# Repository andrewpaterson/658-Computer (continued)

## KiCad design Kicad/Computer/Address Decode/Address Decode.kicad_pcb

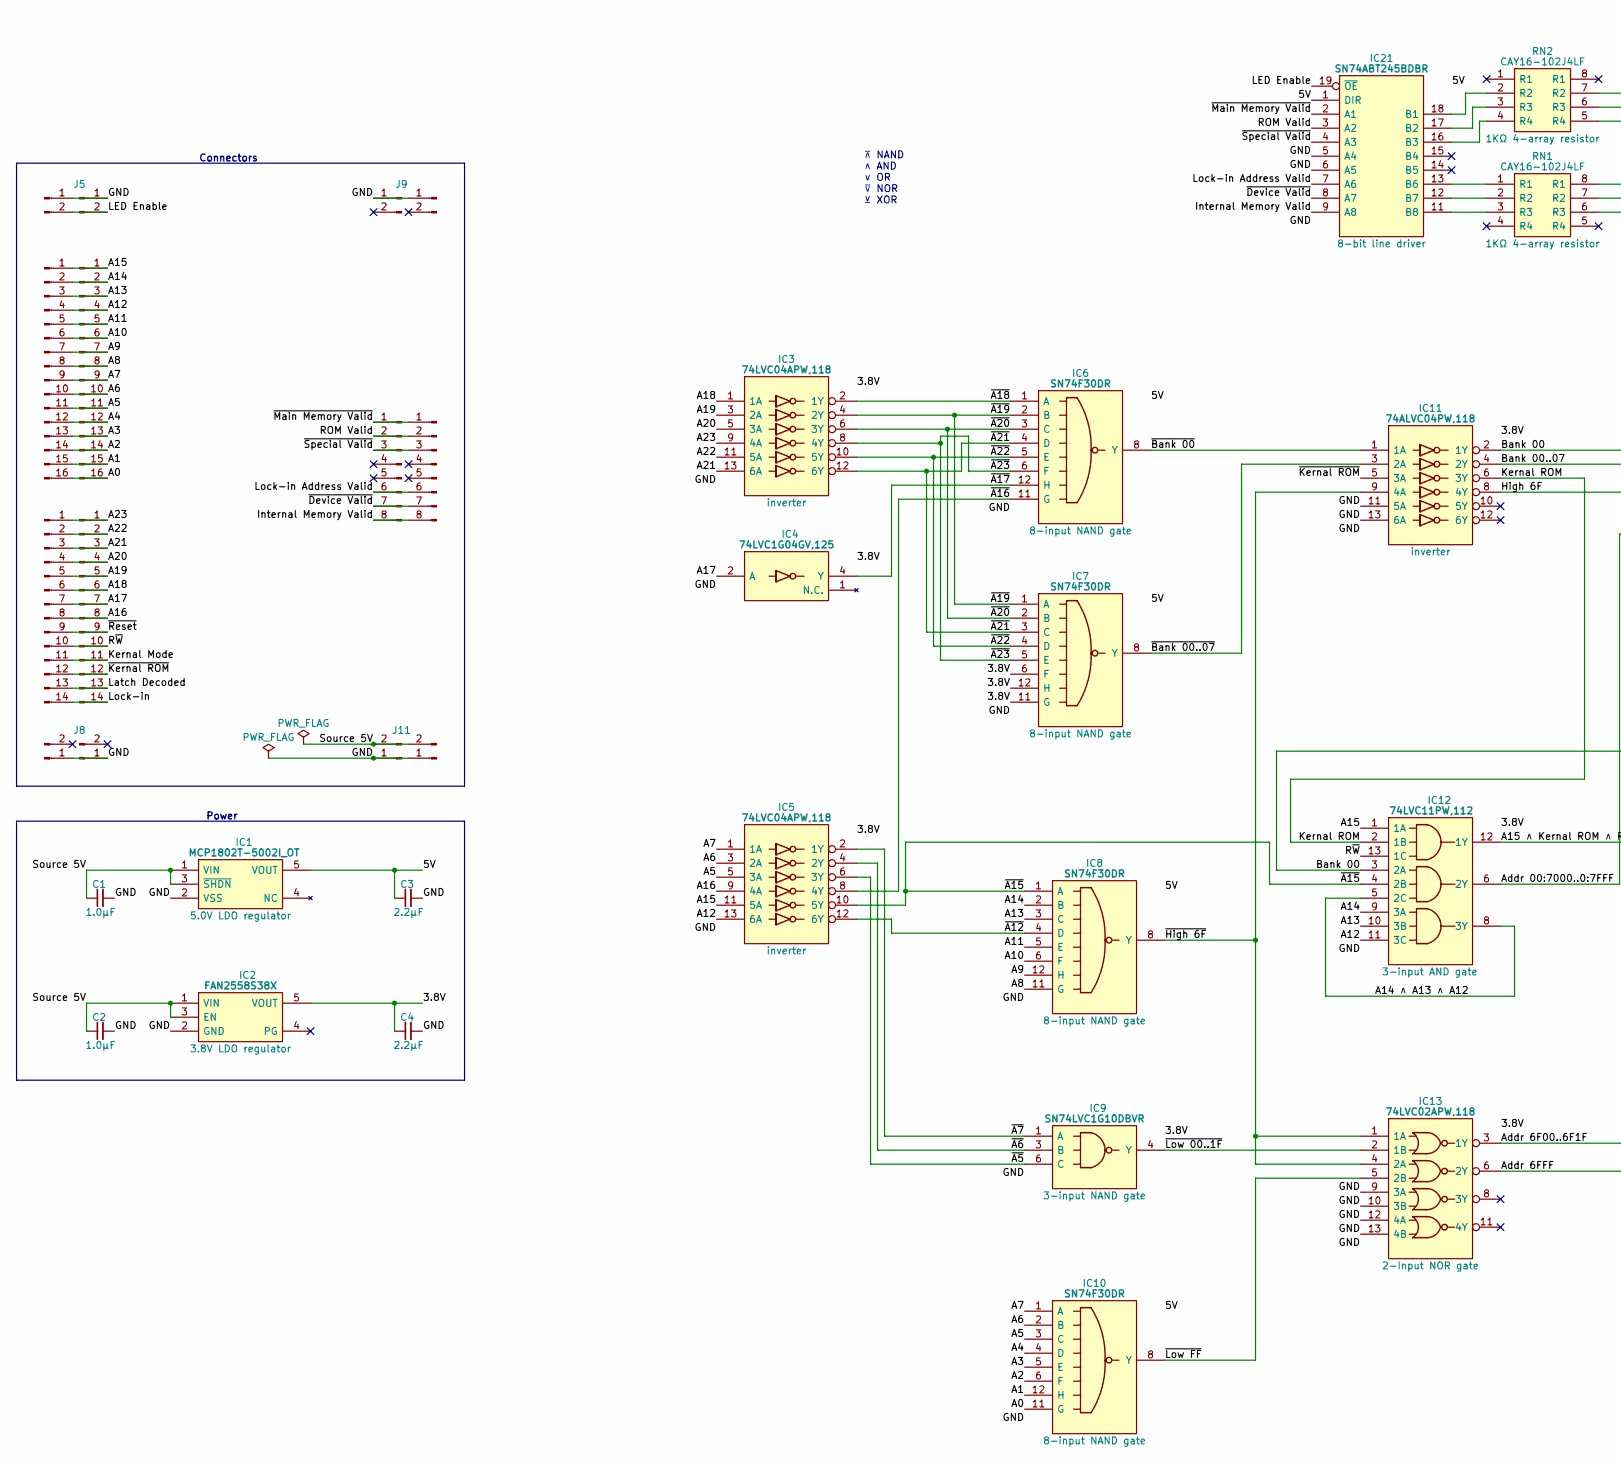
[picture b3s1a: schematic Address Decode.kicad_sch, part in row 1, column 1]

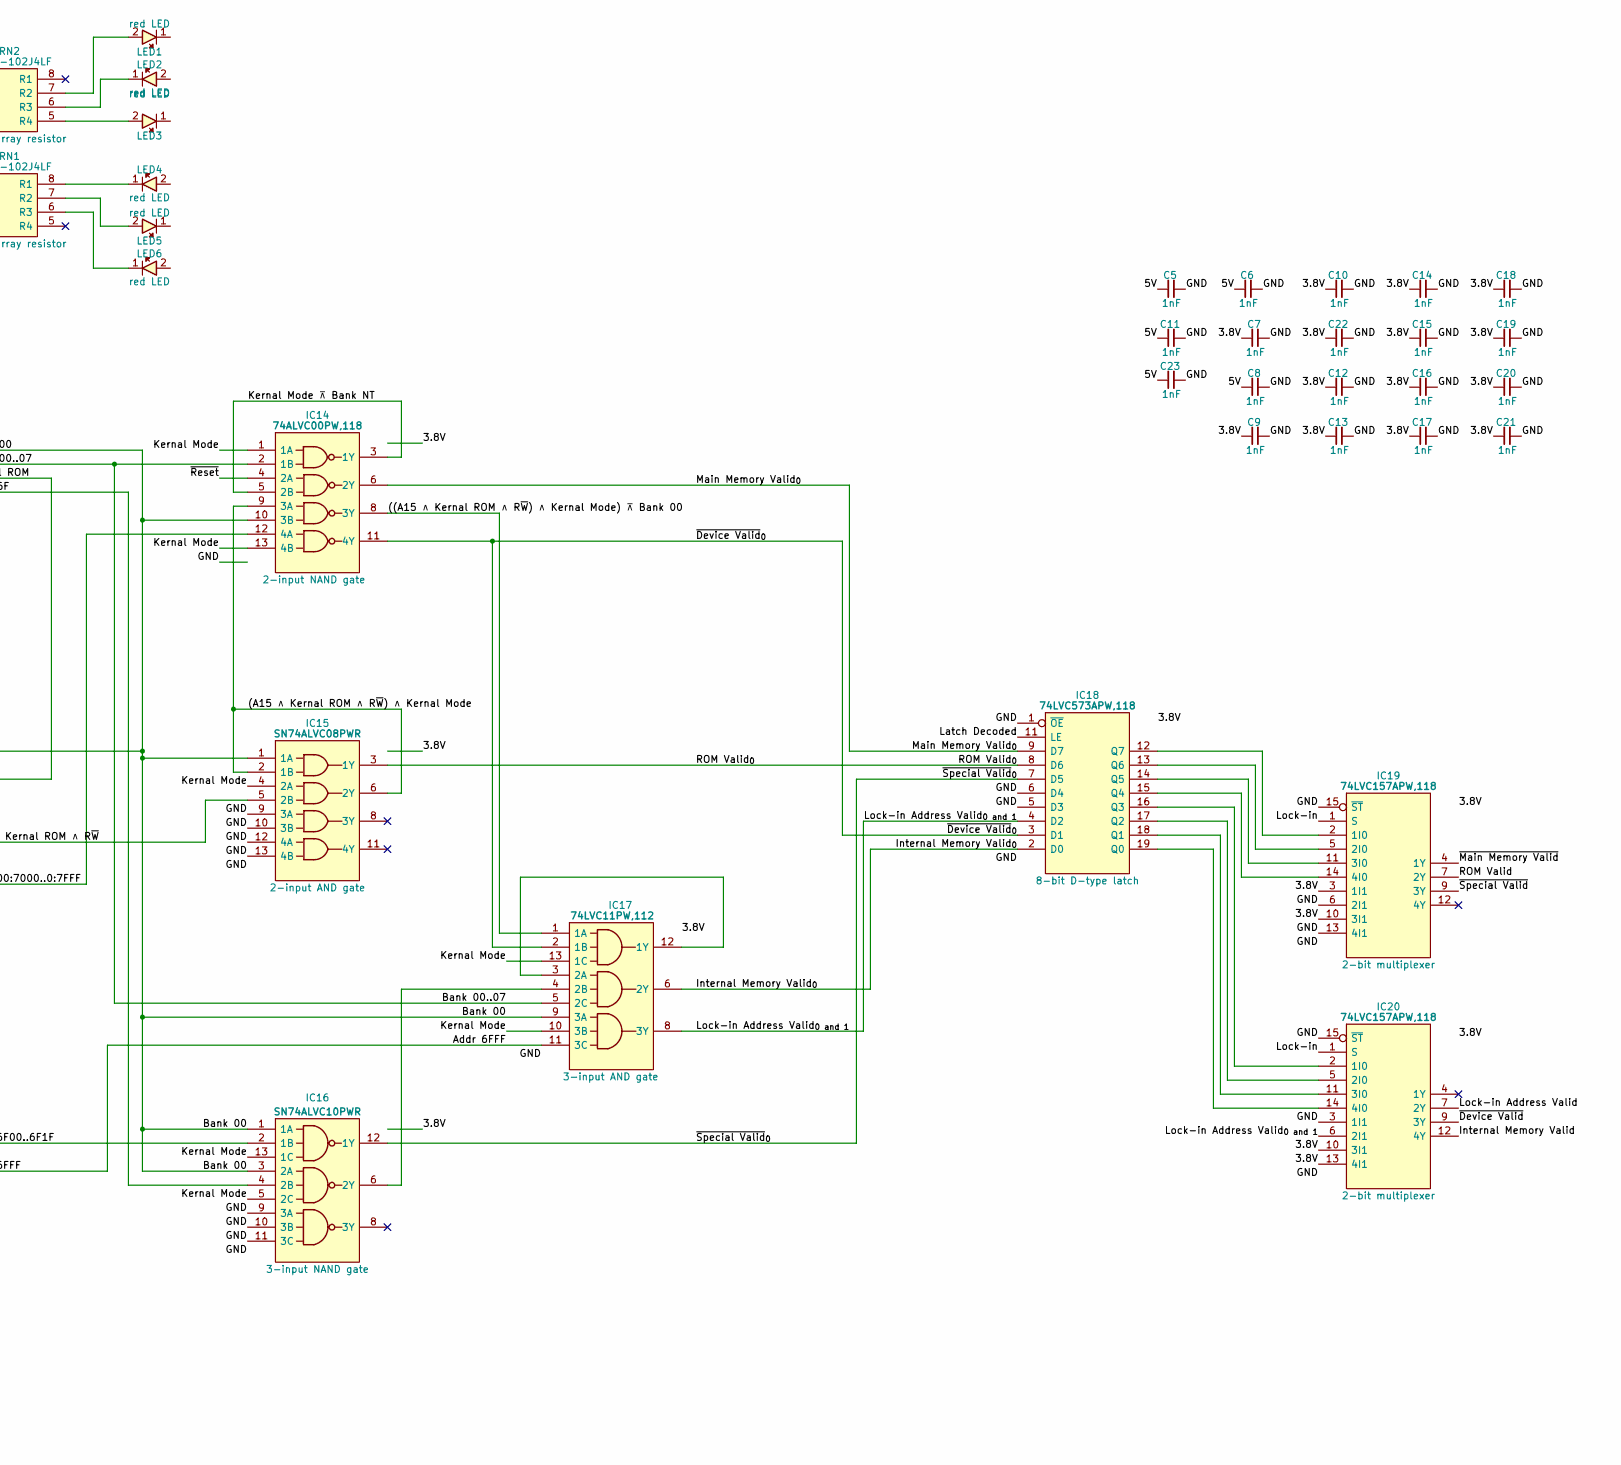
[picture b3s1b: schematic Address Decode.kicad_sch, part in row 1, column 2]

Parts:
C1, C2, C3, C4, C5, C6, C7, C8, C9, C10, C11, C12, C13, C14, C15, C16, C17, C18, C19, C20, C21, C22, C23: C_0805
IC1: MCP1802T-5002I_OT; SOT95P270X145-5N; Manufacturer_Part_Number MCP1802T-5002I/OT; Mouser Part Number 579-MCP1802T-5002IOT
IC2: FAN2558S38X; SOT95P270X145-5N; Manufacturer_Part_Number FAN2558S38X; Mouser Part Number 512-FAN2558S38X
IC3, IC5: 74LVC04APW,118; SOP65P640X110-14N; Manufacturer_Part_Number 74LVC04APW,118; Mouser Part Number 771-74LVC04APW-T
IC4: 74LVC1G04GV,125; SOT95P275X110-5N; Manufacturer_Part_Number 74LVC1G04GV,125; Mouser Part Number 771-74LVC1G04GV
IC6, IC7, IC8, IC10: SN74F30DR; SOIC127P600X175-14N; Manufacturer_Part_Number SN74F30DR; Mouser Part Number 595-SN74F30DR
IC9: SN74LVC1G10DBVR; SOT95P280X145-6N; Manufacturer_Part_Number SN74LVC1G10DBVR; Mouser Part Number 595-SN74LVC1G10DBVR
IC11: 74ALVC04PW,118; SOP65P640X110-14N; Manufacturer_Part_Number 74ALVC04PW,118; Mouser Part Number 771-ALVC04PW118
IC12, IC17: 74LVC11PW,112; SOP65P640X110-14N; Mouser Part Number 771-LVC11PW112
IC13: 74LVC02APW,118; SOP65P640X110-14N; Mouser Part Number 771-74LVC02APW-T
IC14: 74ALVC00PW,118; SOP65P640X110-14N; Mouser Part Number 771-ALVC00PW118
IC15: SN74ALVC08PWR; SOP65P640X120-14N; Manufacturer_Part_Number SN74ALVC08PWR; Mouser Part Number 595-SN74ALVC08PWR
IC16: SN74ALVC10PWR; SOP65P640X120-14N; Manufacturer_Part_Number SN74ALVC10PWR
IC18: 74LVC573APW,118; SOP65P640X110-20N; Mouser Part Number 771-74LVC573APW-T
IC19, IC20: 74LVC157APW,118; SOP65P640X110-16N; Mouser Part Number 771-74LVC157APW-T
IC21: SN74ABT245BDBR; SOP65P780X200-20N; Manufacturer_Part_Number SN74ABT245BDBR; Mouser Part Number 595-SN74ABT245BDBR
J1, J4, J5, J8, J9, J11, J12, J14: Conn_01x02_Male; PinHeader_1x02_P2.54mm_Vertical
J2, J6: Conn_01x16_Male; PinHeader_1x16_P2.54mm_Vertical
J3, J7: Conn_01x14_Male; PinHeader_1x14_P2.54mm_Vertical
J10, J13: Conn_01x08_Male; PinHeader_1x08_P2.54mm_Vertical
LED1, LED2, LED3, LED4, LED5, LED6: 150224SS73100; 150224SS73100A; Manufacturer_Part_Number 150224SS73100; Mouser Part Number 710-150224SS73100
RN1, RN2: CAY16-102J4LF; CAY16-J4; Manufacturer_Part_Number CAY16-102J4LF; Mouser Part Number 652-CAY16-102J4LF

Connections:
/3.8V: C4.1, C7.1, C9.1, C10.1, C12.1, C13.1, C14.1, C15.1, C16.1, C17.1, C18.1, C19.1, C20.1, C21.1, C22.1, IC2.5 (VOUT), IC3.14 (3V), IC4.5 (3V), IC5.14 (3V), IC7.6 (F), IC7.11 (G), IC7.12 (H), IC9.5 (3V), IC11.14 (3V), IC12.14 (3V), IC13.14 (3V), IC14.14 (3V), IC15.14 (3V), IC16.14 (3V), IC17.14 (3V), IC18.20 (3V), IC19.3 (1I1), IC19.10 (3I1), IC19.16 (3V), IC20.10 (3I1), IC20.13 (4I1), IC20.16 (3V)
/5V: C3.1, C5.1, C6.1, C8.1, C11.1, C23.1, IC1.5 (VOUT), IC6.14 (5V), IC7.14 (5V), IC8.14 (5V), IC10.14 (5V), IC21.1 (DIR), IC21.20 (5V)
/((A15 ∧ Kernal ROM ∧ R~W) ∧ Kernal Mode) ⊼ Bank 00: IC14.8 (3Y), IC17.1 (1A)
/(A15 ∧ Kernal ROM ∧ R~W) ∧ Kernal Mode: IC14.9 (3A), IC15.2 (1B), IC15.6 (2Y)
/A0: IC10.11 (G), J2.16, J6.16
/A1: IC10.12 (H), J2.15, J6.15
/A2: IC10.6 (F), J2.14, J6.14
/A3: IC10.5 (E), J2.13, J6.13
/A4: IC10.4 (D), J2.12, J6.12
/A5: IC5.5 (3A), IC10.3 (C), J2.11, J6.11
/A6: IC5.3 (2A), IC10.2 (B), J2.10, J6.10
/A7: IC5.1 (1A), IC10.1 (A), J2.9, J6.9
/A8: IC8.11 (G), J2.8, J6.8
/A9: IC8.12 (H), J2.7, J6.7
/A10: IC8.6 (F), J2.6, J6.6
/A11: IC8.5 (E), J2.5, J6.5
/A12: IC5.13 (6A), IC12.11 (3C), J2.4, J6.4
/A13: IC8.3 (C), IC12.10 (3B), J2.3, J6.3
/A14: IC8.2 (B), IC12.9 (3A), J2.2, J6.2
/A14 ∧ A13 ∧ A12: IC12.5 (2C), IC12.8 (3Y)
/A15: IC5.11 (5A), IC12.1 (1A), J2.1, J6.1
/A15 ∧ Kernal ROM ∧ R~W: IC12.12 (1Y), IC15.5 (2B)
/A16: IC5.9 (4A), J3.8, J7.8
/A17: IC4.2 (A), J3.7, J7.7
/A18: IC3.1 (1A), J3.6, J7.6
/A19: IC3.3 (2A), J3.5, J7.5
/A20: IC3.5 (3A), J3.4, J7.4
/A21: IC3.13 (6A), J3.3, J7.3
/A22: IC3.11 (5A), J3.2, J7.2
/A23: IC3.9 (4A), J3.1, J7.1
/Addr 00:7000..0:7FFF: IC12.6 (2Y), IC14.12 (4A)
/Addr 6F00..6F1F: IC13.3 (1Y), IC16.2 (1B)
/Addr 6FFF: IC13.6 (2Y), IC17.11 (3C)
/Bank 00: IC11.2 (1Y), IC12.3 (2A), IC14.10 (3B), IC15.1 (1A), IC16.1 (1A), IC16.3 (2A), IC17.9 (3A)
/Bank 00..07: IC11.4 (2Y), IC14.2 (1B), IC17.5 (2C)
/GND: C1.2, C2.2, C3.2, C4.2, C5.2, C6.2, C7.2, C8.2, C9.2, C10.2, C11.2, C12.2, C13.2, C14.2, C15.2, C16.2, C17.2, C18.2, C19.2, C20.2, C21.2, C22.2, C23.2, IC1.2 (VSS), IC2.2 (GND), IC3.7 (GND), IC4.3 (GND), IC5.7 (GND), IC6.7 (GND), IC7.7 (GND), IC8.7 (GND), IC9.2 (GND), IC10.7 (GND), IC11.7 (GND), IC11.11 (5A), IC11.13 (6A), IC12.7 (GND), IC13.7 (GND), IC13.9 (3A), IC13.10 (3B), IC13.12 (4A), IC13.13 (4B), IC14.7 (GND), IC15.7 (GND), IC15.9 (3A), IC15.10 (3B), IC15.12 (4A), IC15.13 (4B), IC16.7 (GND), IC16.9 (3A), IC16.10 (3B), IC16.11 (3C), IC17.7 (GND), IC18.1 (~OE), IC18.5 (D3), IC18.6 (D4), IC18.10 (GND), IC19.6 (2I1), IC19.8 (GND), IC19.13 (4I1), IC19.15 (~ST), IC20.3 (1I1), IC20.8 (GND), IC20.15 (~ST), IC21.5 (A4), IC21.6 (A5), IC21.10 (GND), J1.1, J4.1, J5.1, J8.1, J9.1, J11.1, J12.1, J14.1
/High 6F: IC11.8 (4Y), IC16.4 (2B)
/Internal Memory Valid: IC20.12 (4Y), IC21.9 (A8), J10.8, J13.8
/Internal Memory Valid_{0}: IC17.6 (2Y), IC18.2 (D0)
/Kernal Mode: IC14.1 (1A), IC14.13 (4B), IC15.4 (2A), IC16.5 (2C), IC16.13 (1C), IC17.10 (3B), IC17.13 (1C), J3.11, J7.11
/Kernal Mode ⊼ Bank NT: IC14.3 (1Y), IC14.5 (2B)
/Kernal ROM: IC11.6 (3Y), IC12.2 (1B)
/LED Enable: IC21.19 (~OE), J1.2, J5.2
/Latch Decoded: IC18.11 (LE), J3.13, J7.13
/Lock-in: IC19.1 (S), IC20.1 (S), J3.14, J7.14
/Lock-in Address Valid: IC20.7 (2Y), IC21.7 (A6), J10.6, J13.6
/Lock-in Address Valid_{0 and 1}: IC17.8 (3Y), IC18.4 (D2), IC20.6 (2I1)
/Main Memory Valid_{0}: IC14.6 (2Y), IC18.9 (D7)
/ROM Valid: IC19.7 (2Y), IC21.3 (A2), J10.2, J13.2
/ROM Valid_{0}: IC15.3 (1Y), IC18.8 (D6)
/R~W: IC12.13 (1C), J3.10, J7.10
/Source 5V: C1.1, C2.1, IC1.1 (VIN), IC1.3 (~SHDN), IC2.1 (VIN), IC2.3 (EN), J11.2, J14.2
/~A5: IC5.6 (3Y), IC9.6 (C)
/~A6: IC5.4 (2Y), IC9.3 (B)
/~A7: IC5.2 (1Y), IC9.1 (A)
/~A12: IC5.12 (6Y), IC8.4 (D)
/~A15: IC5.10 (5Y), IC8.1 (A), IC12.4 (2B)
/~A16: IC5.8 (4Y), IC6.11 (G)
/~A17: IC4.4 (Y), IC6.12 (H)
/~A18: IC3.2 (1Y), IC6.1 (A)
/~A19: IC3.4 (2Y), IC6.2 (B), IC7.1 (A)
/~A20: IC3.6 (3Y), IC6.3 (C), IC7.2 (B)
/~A21: IC3.12 (6Y), IC6.4 (D), IC7.3 (C)
/~A22: IC3.10 (5Y), IC6.5 (E), IC7.4 (D)
/~A23: IC3.8 (4Y), IC6.6 (F), IC7.5 (E)
/~Bank 00..07: IC7.8 (Y), IC11.3 (2A)
/~Bank 00: IC6.8 (Y), IC11.1 (1A)
/~Device Valid: IC20.9 (3Y), IC21.8 (A7), J10.7, J13.7
/~Device Valid_{0}: IC14.11 (4Y), IC17.2 (1B), IC18.3 (D1)
/~High 6F: IC8.8 (Y), IC11.9 (4A), IC13.1 (1A), IC13.4 (2A)
/~Kernal ROM: IC11.5 (3A), J3.12, J7.12
/~Low 00..1F: IC9.4 (Y), IC13.2 (1B)
/~Low FF: IC10.8 (Y), IC13.5 (2B)
/~Main Memory Valid: IC19.4 (1Y), IC21.2 (A1), J10.1, J13.1
/~Reset: IC14.4 (2A), J3.9, J7.9
/~Special Valid: IC19.9 (3Y), IC21.4 (A3), J10.3, J13.3
/~Special Valid_{0}: IC16.12 (1Y), IC18.7 (D5)
unnamed: IC16.6 (2Y), IC17.4 (2B)
unnamed: IC17.3 (2A), IC17.12 (1Y)
unnamed: IC18.12 (Q7), IC19.2 (1I0)
unnamed: IC18.13 (Q6), IC19.5 (2I0)
unnamed: IC18.14 (Q5), IC19.11 (3I0)
unnamed: IC18.15 (Q4), IC19.14 (4I0)
unnamed: IC18.16 (Q3), IC20.2 (1I0)
unnamed: IC18.17 (Q2), IC20.5 (2I0)
unnamed: IC18.18 (Q1), IC20.11 (3I0)
unnamed: IC18.19 (Q0), IC20.14 (4I0)
unnamed: IC21.11 (B8), RN1.3 (R3)
unnamed: IC21.12 (B7), RN1.2 (R2)
unnamed: IC21.13 (B6), RN1.1 (R1)
unnamed: IC21.16 (B3), RN2.4 (R4)
unnamed: IC21.17 (B2), RN2.3 (R3)
unnamed: IC21.18 (B1), RN2.2 (R2)
unnamed: LED2.1, RN2.6 (R3)
unnamed: LED4.1, RN1.8 (R1)
unnamed: LED6.1, RN1.6 (R3)
unnamed: LED5.2, RN1.7 (R2)
unnamed: LED3.2, RN2.5 (R4)
unnamed: LED1.2, RN2.7 (R2)

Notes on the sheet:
⊼ NAND ∧ AND ∨ OR ⊽ NOR ⊻ XOR
Connectors
Power

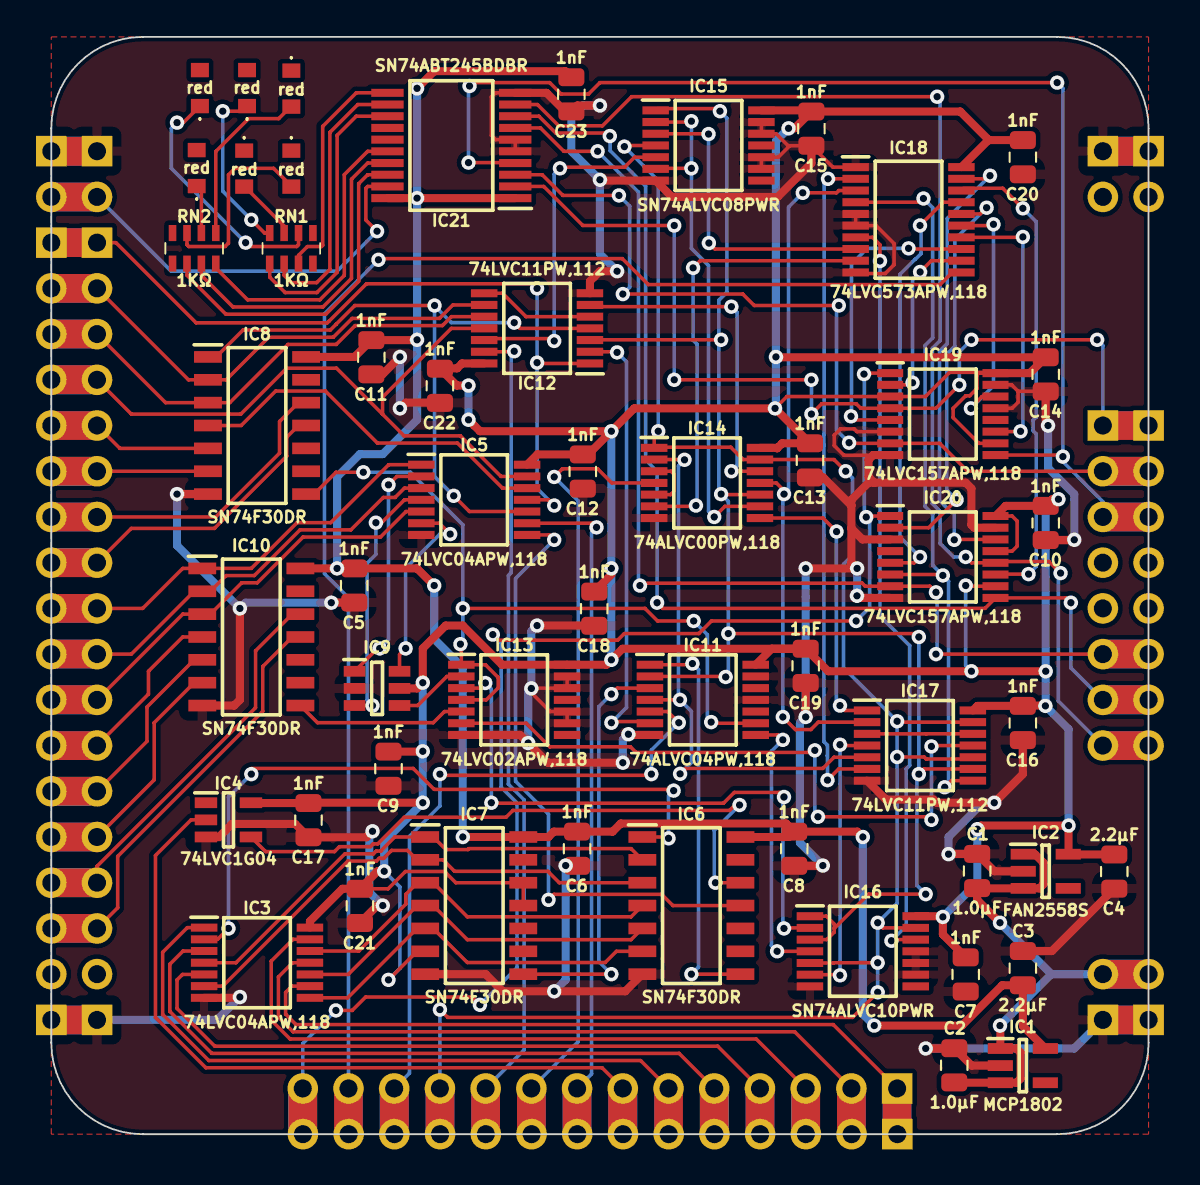
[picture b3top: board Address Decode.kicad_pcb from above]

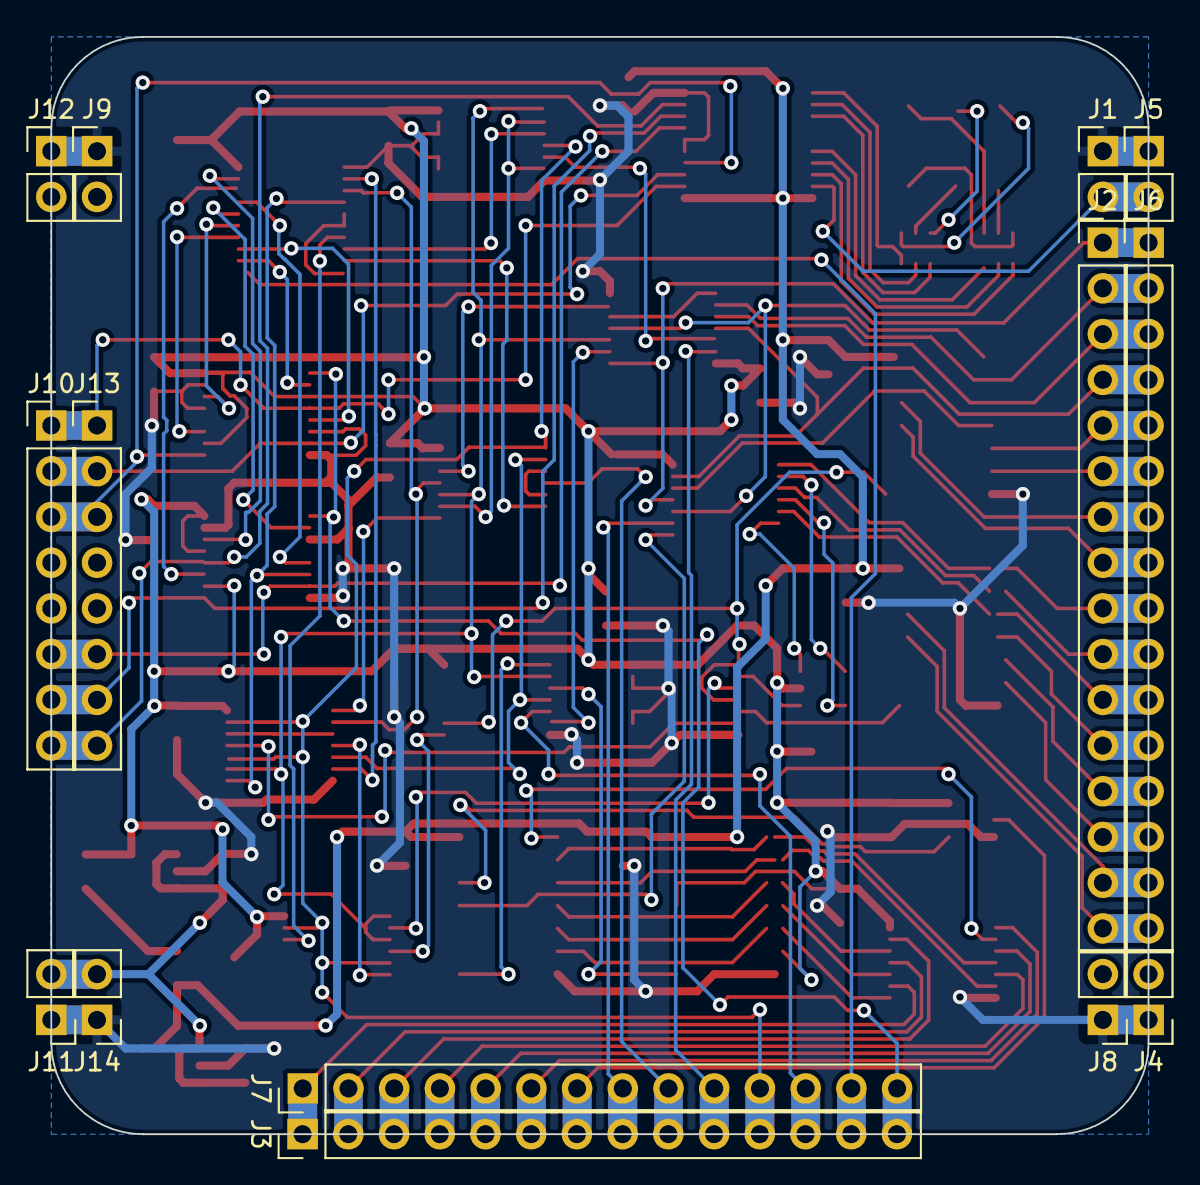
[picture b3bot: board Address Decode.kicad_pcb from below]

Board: 2 copper layers, 61.0 x 61.0 mm, 66 parts (14 on the bottom side), 99 nets.

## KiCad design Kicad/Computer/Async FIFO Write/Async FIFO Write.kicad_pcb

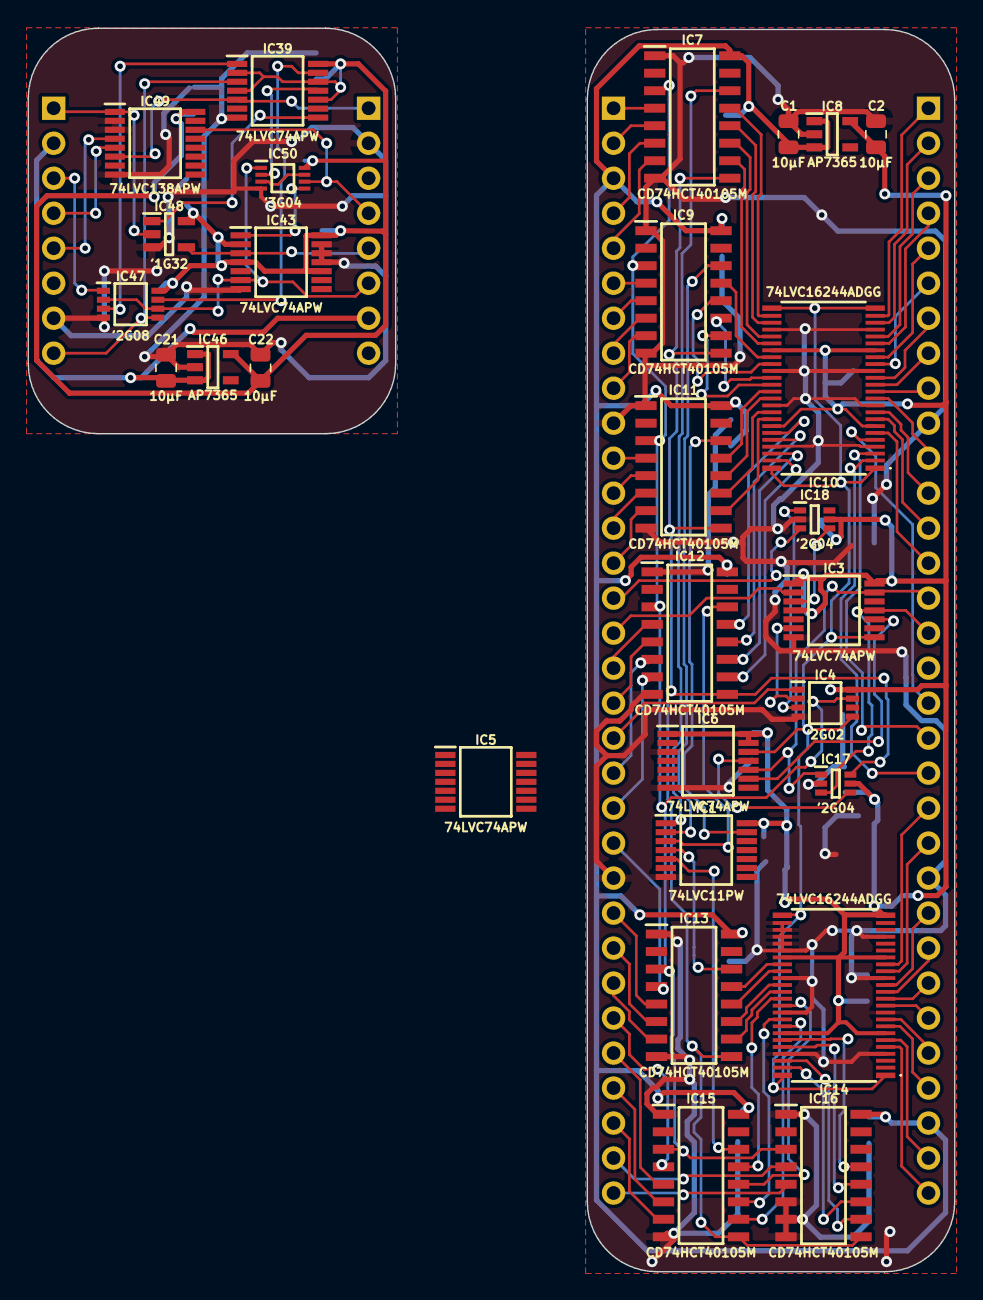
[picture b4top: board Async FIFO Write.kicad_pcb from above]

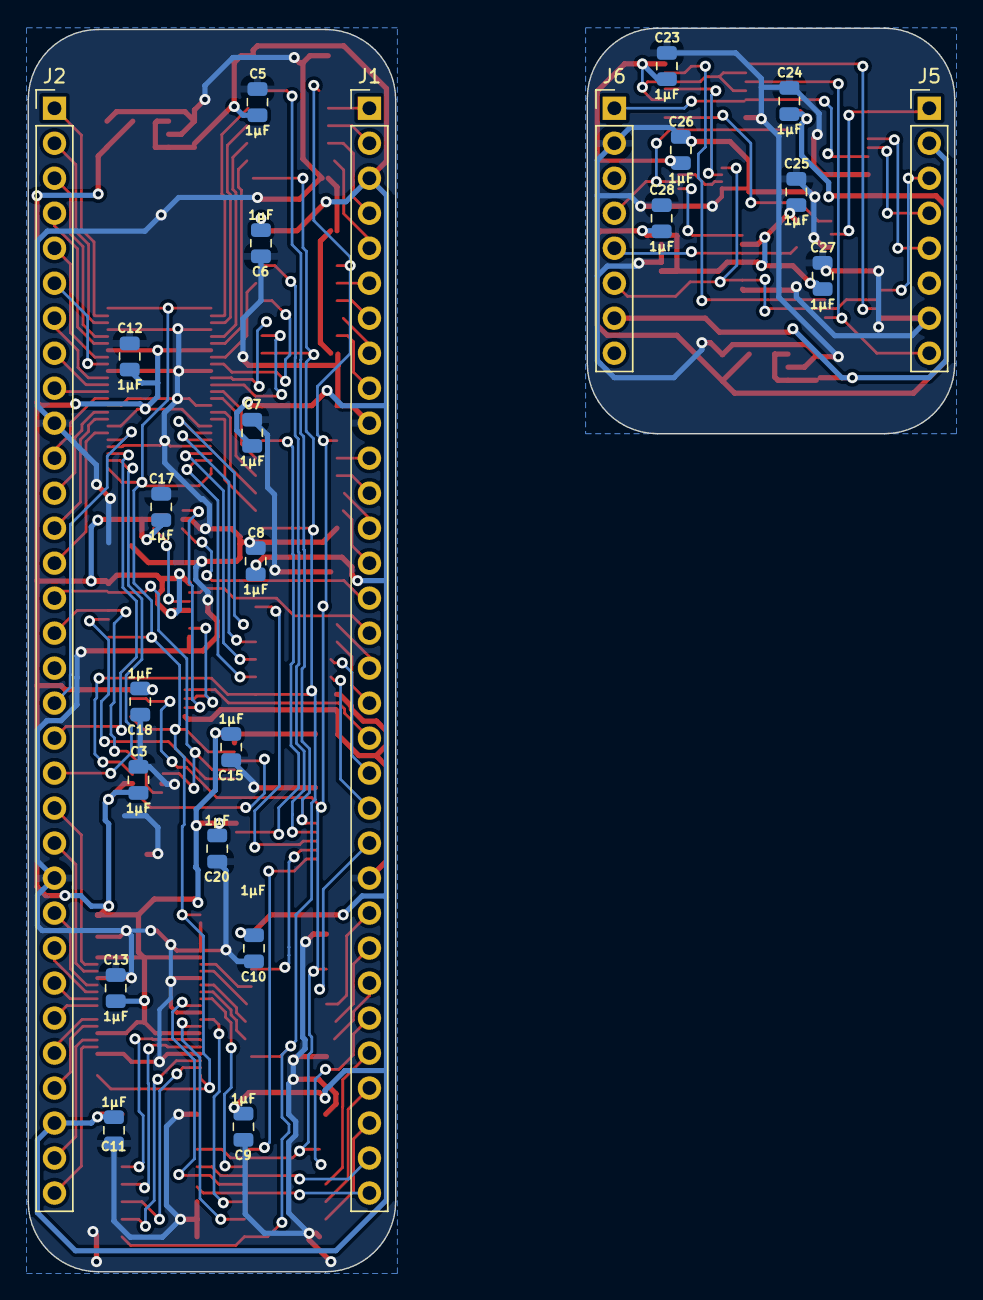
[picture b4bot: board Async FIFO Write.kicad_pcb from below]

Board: 2 copper layers, 67.2 x 90.3 mm, 52 parts (24 on the bottom side), 127 nets.

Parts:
C1, C2, C21, C22: 10µF; C_0805
C3, C5, C6, C7, C8, C9, C10, C11, C12, C13, C15, C17, C18, C20, C23, C24, C25, C26, C27, C28: 1μF; C_0805
IC1: 74LVC11PW,112; SOP65P640X110-14N
IC3, IC5, IC6, IC39, IC43: 74LVC74APW,118; SOP65P640X110-14N
IC4: 74LVC2G02DP,125; SOP65P400X110-8N
IC7, IC9, IC11, IC12, IC13, IC15, IC16: CD74HCT40105M; SOIC127P600X175-16N
IC8, IC46: AP7365-33WG-7; SOT95P285X130-5N
IC10, IC14: 74LVC16244ADGG,112; 74LVC16244ADGG112
IC17, IC18: 74LVC2G04GW-Q100H; SOP65P210X110-6N
IC47: 74LVC2G08DP-Q100H; SOP65P400X110-8N
IC48: 74LVC1G32GV,125; SOT95P275X110-5N
IC49: 74LVC138APW-Q100J; SOP65P640X110-16N
IC50: SN74LVC3G04DCUR; SOP50P310X90-8N
J1, J2: Conn_01x32_Pin; PinHeader_1x32_P2.54mm_Vertical
J5, J6: Conn_01x08_Pin; PinHeader_1x08_P2.54mm_Vertical

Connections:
/Asynchronous Write (FIFO)/2X PHI2: IC18.3 (2A), J1.15
/Asynchronous Write (FIFO)/3.3V: C2.1, C3.1, C12.1, C13.1, C15.1, C17.1, C18.1, C20.1, IC1.14 (3V), IC3.1 (~1RD), IC3.4 (~1SD), IC3.14 (3V), IC4.8 (3V), IC5.2 (1D), IC5.4 (~1SD), IC5.14 (3V), IC6.1 (~1RD), IC6.2 (1D), IC6.4 (~1SD), IC6.13 (~2RD), IC6.14 (3V), IC8.5 (VOUT), IC10.7 (3V), IC10.18 (3V), IC10.31 (3V), IC10.42 (3V), IC14.7 (3V), IC14.18 (3V), IC14.24 (4~OE), IC14.31 (3V), IC14.42 (3V), IC17.5 (3V), IC18.5 (3V)
/Asynchronous Write (FIFO)/5V: C1.1, C5.1, C6.1, C7.1, C8.1, C9.1, C10.1, C11.1, IC7.16 (5V), IC8.1 (VIN), IC8.3 (EN), IC9.16 (5V), IC11.16 (5V), IC12.16 (5V), IC13.16 (5V), IC15.16 (5V), IC16.16 (5V), J1.3, J2.30
/Asynchronous Write (FIFO)/A0: IC11.4 (D0), J1.11
/Asynchronous Write (FIFO)/A1: IC11.5 (D1), J1.12
/Asynchronous Write (FIFO)/A2: IC11.6 (D2), J1.13
/Asynchronous Write (FIFO)/A3: IC11.7 (D3), J1.14
/Asynchronous Write (FIFO)/A4: IC12.4 (D0), J1.17
/Asynchronous Write (FIFO)/A5: IC12.5 (D1), J1.18
/Asynchronous Write (FIFO)/A6: IC12.6 (D2), J1.20
/Asynchronous Write (FIFO)/A7: IC12.7 (D3), J1.21
/Asynchronous Write (FIFO)/A8: IC13.4 (D0), J1.22
/Asynchronous Write (FIFO)/A9: IC13.5 (D1), J1.24
/Asynchronous Write (FIFO)/A10: IC13.6 (D2), J1.25
/Asynchronous Write (FIFO)/A11: IC13.7 (D3), J1.26
/Asynchronous Write (FIFO)/A12: IC15.4 (D0), J1.27
/Asynchronous Write (FIFO)/A13: IC15.5 (D1), J1.28
/Asynchronous Write (FIFO)/A14: IC15.6 (D2), J1.29
/Asynchronous Write (FIFO)/A15: IC15.7 (D3), J1.30
/Asynchronous Write (FIFO)/A16: IC16.4 (D0), J1.31
/Asynchronous Write (FIFO)/A17: IC16.5 (D1), J1.32
/Asynchronous Write (FIFO)/A_{OUT}0: IC10.37 (2A3), IC11.13 (Q0)
/Asynchronous Write (FIFO)/A_{OUT}1: IC10.38 (2A2), IC11.12 (Q1)
/Asynchronous Write (FIFO)/A_{OUT}2: IC10.40 (2A1), IC11.11 (Q2)
/Asynchronous Write (FIFO)/A_{OUT}3: IC10.41 (2A0), IC11.10 (Q3)
/Asynchronous Write (FIFO)/A_{OUT}4: IC10.43 (1A3), IC12.13 (Q0)
/Asynchronous Write (FIFO)/A_{OUT}5: IC10.44 (1A2), IC12.12 (Q1)
/Asynchronous Write (FIFO)/A_{OUT}6: IC10.46 (1A1), IC12.11 (Q2)
/Asynchronous Write (FIFO)/A_{OUT}7: IC10.47 (1A0), IC12.10 (Q3)
/Asynchronous Write (FIFO)/A_{OUT}8: IC13.13 (Q0), IC14.32 (3A3)
/Asynchronous Write (FIFO)/A_{OUT}9: IC13.12 (Q1), IC14.33 (3A2)
/Asynchronous Write (FIFO)/A_{OUT}10: IC13.11 (Q2), IC14.35 (3A1)
/Asynchronous Write (FIFO)/A_{OUT}11: IC13.10 (Q3), IC14.36 (3A0)
/Asynchronous Write (FIFO)/A_{OUT}12: IC14.37 (2A3), IC15.13 (Q0)
/Asynchronous Write (FIFO)/A_{OUT}13: IC14.38 (2A2), IC15.12 (Q1)
/Asynchronous Write (FIFO)/A_{OUT}14: IC14.40 (2A1), IC15.11 (Q2)
/Asynchronous Write (FIFO)/A_{OUT}15: IC14.41 (2A0), IC15.10 (Q3)
/Asynchronous Write (FIFO)/A_{OUT}16: IC14.43 (1A3), IC16.13 (Q0)
/Asynchronous Write (FIFO)/A_{OUT}17: IC14.44 (1A2), IC16.12 (Q1)
/Asynchronous Write (FIFO)/A_{OUT}18: IC14.47 (1A0), IC16.11 (Q2)
/Asynchronous Write (FIFO)/A_{OUT}19: IC14.46 (1A1), IC16.10 (Q3)
/Asynchronous Write (FIFO)/A_{W}0: IC10.12 (2Y3), J2.9
/Asynchronous Write (FIFO)/A_{W}1: IC10.11 (2Y2), J2.11
/Asynchronous Write (FIFO)/A_{W}2: IC10.9 (2Y1), J2.12
/Asynchronous Write (FIFO)/A_{W}3: IC10.8 (2Y0), J2.13
/Asynchronous Write (FIFO)/A_{W}4: IC10.6 (1Y3), J2.14
/Asynchronous Write (FIFO)/A_{W}5: IC10.5 (1Y2), J2.18
/Asynchronous Write (FIFO)/A_{W}6: IC10.3 (1Y1), J2.19
/Asynchronous Write (FIFO)/A_{W}7: IC10.2 (1Y0), J2.20
/Asynchronous Write (FIFO)/A_{W}8: IC14.17 (3Y3), J2.21
/Asynchronous Write (FIFO)/A_{W}9: IC14.16 (3Y2), J2.22
/Asynchronous Write (FIFO)/A_{W}10: IC14.14 (3Y1), J2.24
/Asynchronous Write (FIFO)/A_{W}11: IC14.13 (3Y0), J2.25
/Asynchronous Write (FIFO)/A_{W}12: IC14.12 (2Y3), J2.26
/Asynchronous Write (FIFO)/A_{W}13: IC14.11 (2Y2), J2.27
/Asynchronous Write (FIFO)/A_{W}14: IC14.9 (2Y1), J2.28
/Asynchronous Write (FIFO)/A_{W}15: IC14.8 (2Y0), J2.29
/Asynchronous Write (FIFO)/A_{W}16: IC14.6 (1Y3), J2.31
/Asynchronous Write (FIFO)/A_{W}17: IC14.5 (1Y2), J2.32
/Asynchronous Write (FIFO)/D0: IC7.4 (D0), J1.1
/Asynchronous Write (FIFO)/D1: IC7.5 (D1), J1.2
/Asynchronous Write (FIFO)/D2: IC7.6 (D2), J1.4
/Asynchronous Write (FIFO)/D3: IC7.7 (D3), J1.5
/Asynchronous Write (FIFO)/D4: IC9.4 (D0), J1.6
/Asynchronous Write (FIFO)/D5: IC9.5 (D1), J1.7
/Asynchronous Write (FIFO)/D6: IC9.6 (D2), J1.8
/Asynchronous Write (FIFO)/D7: IC9.7 (D3), J1.9
/Asynchronous Write (FIFO)/DOR0: IC1.1 (1A), IC7.14 (DOR)
/Asynchronous Write (FIFO)/DOR0·DOR1·DOR2: IC1.10 (3B), IC1.12 (1Y)
/Asynchronous Write (FIFO)/DOR1: IC1.2 (1B), IC9.14 (DOR)
/Asynchronous Write (FIFO)/DOR2: IC1.13 (1C), IC11.14 (DOR)
/Asynchronous Write (FIFO)/DOR3: IC1.3 (2A), IC12.14 (DOR)
/Asynchronous Write (FIFO)/DOR3·DOR4·DOR5: IC1.6 (2Y), IC1.11 (3C)
/Asynchronous Write (FIFO)/DOR4: IC1.4 (2B), IC13.14 (DOR)
/Asynchronous Write (FIFO)/DOR5: IC1.5 (2C), IC15.14 (DOR)
/Asynchronous Write (FIFO)/DOR6: IC1.9 (3A), IC16.14 (DOR)
/Asynchronous Write (FIFO)/D_{OUT}0: IC7.13 (Q0), IC10.26 (4A3)
/Asynchronous Write (FIFO)/D_{OUT}1: IC7.12 (Q1), IC10.27 (4A2)
/Asynchronous Write (FIFO)/D_{OUT}2: IC7.11 (Q2), IC10.29 (4A1)
/Asynchronous Write (FIFO)/D_{OUT}3: IC7.10 (Q3), IC10.30 (4A0)
/Asynchronous Write (FIFO)/D_{OUT}4: IC9.13 (Q0), IC10.32 (3A3)
/Asynchronous Write (FIFO)/D_{OUT}5: IC9.12 (Q1), IC10.33 (3A2)
/Asynchronous Write (FIFO)/D_{OUT}6: IC9.11 (Q2), IC10.35 (3A1)
/Asynchronous Write (FIFO)/D_{OUT}7: IC9.10 (Q3), IC10.36 (3A0)
/Asynchronous Write (FIFO)/D_{W}0: IC10.23 (4Y3), J2.1
/Asynchronous Write (FIFO)/D_{W}1: IC10.22 (4Y2), J2.2
/Asynchronous Write (FIFO)/D_{W}2: IC10.20 (4Y1), J2.3
/Asynchronous Write (FIFO)/D_{W}3: IC10.19 (4Y0), J2.4
/Asynchronous Write (FIFO)/D_{W}4: IC10.17 (3Y3), J2.5
/Asynchronous Write (FIFO)/D_{W}5: IC10.16 (3Y2), J2.6
/Asynchronous Write (FIFO)/D_{W}6: IC10.14 (3Y1), J2.7
/Asynchronous Write (FIFO)/D_{W}7: IC10.13 (3Y0), J2.8
/Asynchronous Write (FIFO)/Data Out Ready: IC1.8 (3Y), IC5.3 (1CP), IC5.10 (~2SD)
/Asynchronous Write (FIFO)/Data Out Ready Flop: IC3.12 (2D), IC5.5 (1Q)
/Asynchronous Write (FIFO)/GND: C1.2, C2.2, C3.2, C5.2, C6.2, C7.2, C8.2, C9.2, C10.2, C11.2, C12.2, C13.2, C15.2, C17.2, C18.2, C20.2, IC1.7 (GND), IC3.7 (GND), IC4.4 (GND), IC5.7 (GND), IC5.11 (2CP), IC5.12 (2D), IC6.3 (1CP), IC6.7 (GND), IC7.1 (~EN(TSC)), IC7.8 (GND), IC8.2 (GND), IC9.1 (~EN(TSC)), IC9.8 (GND), IC10.4 (GND), IC10.10 (GND), IC10.15 (GND), IC10.21 (GND), IC10.28 (GND), IC10.34 (GND), IC10.39 (GND), IC10.45 (GND), IC11.1 (~EN(TSC)), IC11.8 (GND), IC12.1 (~EN(TSC)), IC12.8 (GND), IC13.1 (~EN(TSC)), IC13.8 (GND), IC14.4 (GND), IC14.10 (GND), IC14.15 (GND), IC14.21 (GND), IC14.26 (4A3), IC14.27 (4A2), IC14.28 (GND), IC14.29 (4A1), IC14.30 (4A0), IC14.34 (GND), IC14.39 (GND), IC14.45 (GND), IC15.1 (~EN(TSC)), IC15.8 (GND), IC16.1 (~EN(TSC)), IC16.6 (D2), IC16.7 (D3), IC16.8 (GND), IC17.2 (GND), IC18.2 (GND), J1.10, J1.23, J2.10, J2.23
/Asynchronous Write (FIFO)/PHI2: IC3.2 (1D), J1.16
/Asynchronous Write (FIFO)/Pixel Clock: IC3.11 (2CP), IC17.3 (2A), J2.16
/Asynchronous Write (FIFO)/RESET: IC7.9 (MR), IC9.9 (MR), IC11.9 (MR), IC12.9 (MR), IC13.9 (MR), IC15.9 (MR), IC16.9 (MR), IC17.6 (1Y)
/Asynchronous Write (FIFO)/SI: IC4.7 (1Y), IC7.3 (SI), IC9.3 (SI), IC11.3 (SI), IC12.3 (SI), IC13.3 (SI), IC15.3 (SI), IC16.3 (SI)
/Asynchronous Write (FIFO)/~2X PHI2: IC3.3 (1CP), IC18.4 (2Y)
/Asynchronous Write (FIFO)/~CS: IC4.1 (1A), J1.19
/Asynchronous Write (FIFO)/~Clear Data Write: IC3.10 (~2SD), IC5.1 (~1RD), IC5.13 (~2RD), IC6.9 (2Q)
/Asynchronous Write (FIFO)/~Data Write: IC3.8 (~2Q), IC4.5 (2A), IC4.6 (2B), IC6.12 (2D), IC10.1 (1~OE), IC10.24 (4~OE), IC10.25 (3~OE), IC10.48 (2~OE), IC14.1 (1~OE), IC14.25 (3~OE), IC14.48 (2~OE)
/Asynchronous Write (FIFO)/~Data Write_{OUT}: IC18.6 (1Y), J2.17
/Asynchronous Write (FIFO)/~Pixel Clock: IC6.11 (2CP), IC17.4 (2Y)
/Asynchronous Write (FIFO)/~RESET: IC3.13 (~2RD), IC6.10 (~2SD), IC17.1 (1A), J2.15
/Asynchronous Write (FIFO)/~SO: IC5.9 (2Q), IC7.15 (~SO), IC9.15 (~SO), IC11.15 (~SO), IC12.15 (~SO), IC13.15 (~SO), IC15.15 (~SO), IC16.15 (~SO)
/Asynchronous Write (FIFO)/~Video SI: IC3.6 (~1Q), IC4.2 (1B)
/Asynchronous Write (PHI2 Hold)/3.3V: C22.1, C23.1, C24.1, C25.1, C26.1, C27.1, C28.1, IC39.2 (1D), IC39.4 (~1SD), IC39.10 (~2SD), IC39.12 (2D), IC39.14 (3V), IC43.2 (1D), IC43.4 (~1SD), IC43.10 (~2SD), IC43.14 (3V), IC46.5 (VOUT), IC47.8 (3V), IC48.5 (3V), IC49.16 (3V), IC50.8 (3V)
/Asynchronous Write (PHI2 Hold)/5V: C21.1, IC46.1 (VIN), IC46.3 (EN), J5.2, J6.7
/Asynchronous Write (PHI2 Hold)/GND: C21.2, C22.2, C23.2, C24.2, C25.2, C26.2, C27.2, C28.2, IC39.7 (GND), IC43.7 (GND), IC43.11 (2CP), IC43.12 (2D), IC43.13 (~2RD), IC46.2 (GND), IC47.4 (GND), IC48.3 (GND), IC49.2 (A1), IC49.3 (A2), IC49.8 (GND), IC50.4 (GND), J5.7, J6.2
/Asynchronous Write (PHI2 Hold)/PHI2: IC39.3 (1CP), IC47.5 (2A), J5.8
/Asynchronous Write (PHI2 Hold)/PHI2 Risen: IC39.5 (1Q), IC49.6 (E3), J6.1
/Asynchronous Write (PHI2 Hold)/Pixel Clock: IC48.2 (A), IC49.1 (A0), J5.1
/Asynchronous Write (PHI2 Hold)/Video Write Waiting: IC39.11 (2CP), IC50.2 (3Y)
/Asynchronous Write (PHI2 Hold)/~CS: IC49.4 (~E1), J5.5
/Asynchronous Write (PHI2 Hold)/~RESET: IC47.1 (1A), J5.3
/Asynchronous Write (PHI2 Hold)/~Video Write Done: IC43.6 (~1Q), IC47.2 (1B), IC47.6 (2B), IC50.1 (1A), J6.6
/Asynchronous Write (PHI2 Hold)/~Video Write Progress: IC39.8 (~2Q), IC48.1 (B)
/Asynchronous Write (PHI2 Hold)/~Video Write Waiting: IC49.14 (~Y1), IC50.6 (3A), J6.4
/Asynchronous Write (PHI2 Hold)/~Video Write: IC43.3 (1CP), IC48.4 (Y), J6.5
/Asynchronous Write (PHI2 Hold)/~WD: IC49.5 (~E2), J5.4
unnamed: IC4.3 (2Y), IC18.1 (1A)
unnamed: IC39.1 (~1RD), IC47.3 (2Y)
unnamed: IC39.13 (~2RD), IC47.7 (1Y)
unnamed: IC43.1 (~1RD), IC50.5 (2Y)
unnamed: IC50.3 (2A), IC50.7 (1Y)
